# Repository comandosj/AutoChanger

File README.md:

AutoChanger - A Knitting Machine Auto Colour Changer to replace a Brother KRC-900
=============

This project was designed to provide a lower cost replacement for the commercial auto colour changer available from Brother for their 1980's electronic knitting machines.

You can read about the progress of this design at the following links:

[Building a better colour changer - Part 1 - Designing Hardware](http://heartofpluto.co/2017/04/25/building-a-better-colour-changer-part-1-designing-hardware/)

[Building a better colour changer - Part 2 - Firing the lasers](http://heartofpluto.co/2017/05/08/building-a-better-colour-changer-part-2-firing-the-lasers/)

[Building a Better Colour Changer  Part 3  Revising the design](http://heartofpluto.co/2017/10/21/building-a-better-colour-changer-part-3-revising-the-design/)

The Arduino Nano based controller.

[Schematic Design](Controller/AutoChanger.pdf?raw=true "Schematic")

FEATURES
--------

* Arduino Uno compatible.
* Automatically change between 4 different colours.
* Audio guides.
* Programable colour order.

CREDITS
------------

This project was designed in 2017 by John and Sarah Spencer
 - [John Spencer](https://github.com/mage0r)
 - [Sarah Spencer](https://github.com/chixor)

Check us out at [Heart Of Pluto](http://heartofpluto.co)

Made at hackmelbourne.org!

SPECIAL THANKS
------------

To the HackMelbourne (CCHS, http://hackmelbourne.org) community of Melbourne, Australia.

To all other open-source developers whose countless hours supported every other aspect of this design.

DISTRIBUTION
------------
The specific terms of distribution of this project are governed by the
license referenced below. Please contact the copyright owner if you wish to modify the board for distribution. Please utilize this design for personal or research projects. Please acknowledge all contributors.

LICENSE
-------
Licensed under the TAPR Open Hardware License (www.tapr.org/OHL).
The "license" sub-folder also contains a copy of this license in plain text format.

Copyright John Spencer, Sarah Spencer, 2017

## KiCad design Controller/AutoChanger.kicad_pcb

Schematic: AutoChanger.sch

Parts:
C1, C2, C10, C11, C12, C13: 1uF; C_0603_HandSoldering
C8: 100nF; C_0603_HandSoldering
P1: CONNECT; Pin_Header_Straight_2x02_Pitch2.54mm
P3: 1; Pin_Header_Straight_1x03_Pitch2.54mm
P4: 2; Pin_Header_Straight_1x03_Pitch2.54mm
P5: 3; Pin_Header_Straight_1x03_Pitch2.54mm
P6: 4; Pin_Header_Straight_1x03_Pitch2.54mm
P7: 6; Pin_Header_Straight_1x03_Pitch2.54mm
P8, P9: M3; 1pin
P10, P11: SENSOR; Pin_Header_Straight_1x03_Pitch2.54mm
P12: LOGO; logo
P13: 5; Pin_Header_Straight_1x03_Pitch2.54mm
R1, R5, R7, R8, R9, R10, R11: 10K; R_0603_HandSoldering
R4: 220R; R_0603_HandSoldering
R12: 100; R_0603_HandSoldering
SP1: SPEAKER; Buzzer_12x9.5RM7.6
SW1: RESET; SW_PUSH_SMALL
SW2: 1; SW_PUSH_SMALL
SW3: 2; SW_PUSH_SMALL
SW4: 3; SW_PUSH_SMALL
SW5: 4; SW_PUSH_SMALL
SW6: PGRM; SW_PUSH_SMALL
U1: arduino_nano; nano
U2: STATUS; LED_WS2812B-PLCC4
U3: ITR9606-F; ITR9606

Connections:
+5V: C1.2, C2.2, C8.1, C10.2, C11.2, C12.2, C13.2, P1.4, P3.2, P4.2, P5.2, P6.2, P7.2, P10.1, P11.1, P13.2, R1.1, R4.1, R7.1, R8.1, R9.1, R10.1, R11.1, U1.12, U2.1; also elsewhere on the board
/3V3: U1.2
/A0: P3.3, U1.4
/A1: P4.3, U1.5
/A2: P5.3, U1.6
/A3: P6.3, U1.7
/A4: P13.3, U1.8
/A5: P7.3, U1.9
/A6: U1.10
/A7: U1.11
/AREF: U1.3
/D2: U1.20
/D3: R12.1, U1.21
/D4: U1.22, U2.4
/D5: P1.2, U1.23
/D6: R11.2, SW6.1, U1.24
/D7: R10.2, SW5.1, U1.25
/D8: R9.2, SW4.1, U1.26
/D9: R8.2, SW3.1, U1.27
/D10: R7.2, SW2.1, U1.28
/D11: P1.3, U1.29
/D12: U1.30
/D13: P10.2, P11.2, R5.1, U1.1, U3.4
/RESET: R1.2, SW1.1, U1.13, U1.18
/RXD: U1.17
/TXD: U1.16
/VIN: U1.15
GND: C1.1, C2.1, C8.2, C10.1, C11.1, C12.1, C13.1, P1.1, P3.1, P4.1, P5.1, P6.1, P7.1, P10.3, P11.3, P13.1, R5.2, SP1.1, SW1.2, SW2.2, SW3.2, SW4.2, SW5.2, SW6.2, U1.14, U1.19, U2.3, U3.2
unnamed 30: U3.3; also elsewhere on the board
unnamed: R4.2, U3.1
unnamed: R12.2, SP1.2

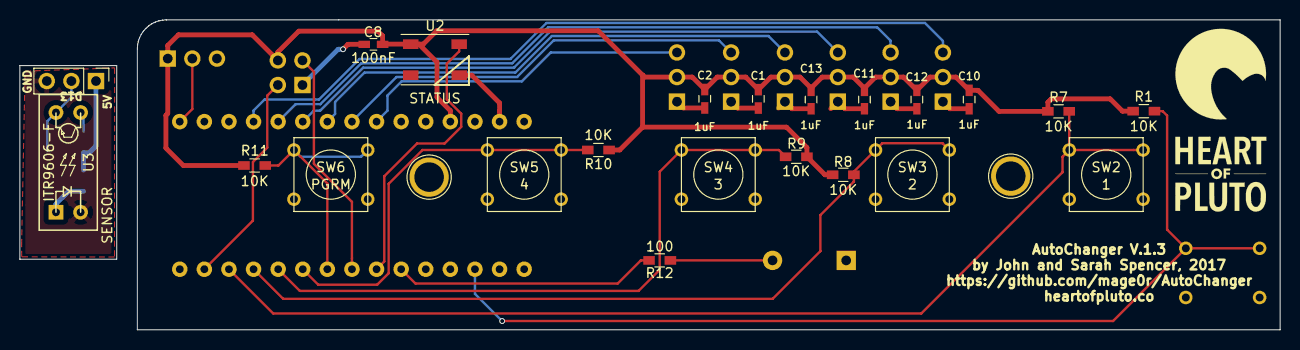
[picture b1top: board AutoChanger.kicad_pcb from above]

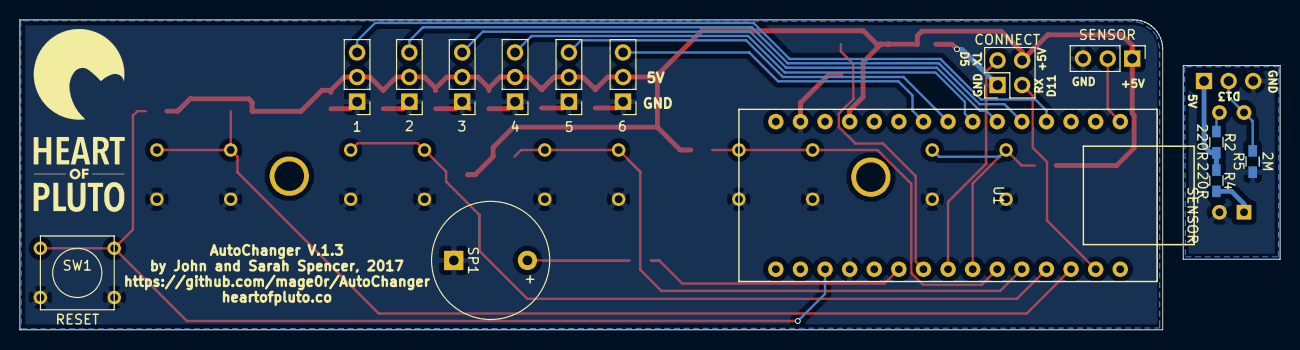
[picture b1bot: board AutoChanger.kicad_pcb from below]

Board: 2 copper layers, 130.1 x 32.0 mm, 40 parts (15 on the bottom side), 22 nets.

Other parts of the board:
P12#2: LOGO; logo
R2: 220R; R_0603_HandSoldering

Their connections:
+5V: R2.1; also elsewhere on the board
unnamed 30: R2.2; also elsewhere on the board

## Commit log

2017-05-14 :confetti_ball: Added .gitattributes & .gitignore files
2017-05-14 Initial Upload
2017-05-19 Added a buzzer and moved pins.
2017-05-27 Adding schematic pdfs and license
2017-05-27 Hardware design Sketchup files added
2017-05-27 Added Readme file.
2017-05-27 typos
2017-05-27 Updated design.
2017-05-28 Optical pickup was too small in design
2017-06-25 Updated board design.
    Heaps more caps. Thanks @projectgus
2017-06-25 Revised the size of gear shaft.
2017-08-19 Updated hardware design
    Getting closer and closer to having all the angles right.
2017-08-25 Updated design
2017-09-11 Updated circuit board
2017-10-05 Updated version
2017-10-19 New Nano version
2017-10-19 updated submodules
2017-10-19 Updated 3d settings.
2017-10-19 Adding Software
2018-09-05 Updated designs across the board
    So, lots of small changes as I've tweaked the design.
    In order to improve manufacturing, I've changed to 3d printing the main body.
2018-09-05 Lets ignore stl files
2018-10-23 Updated sub board
2018-10-23 File cleanup
2018-10-23 Cleaned up readme
2018-10-23 Updated image link.
2018-11-09 Big code update. Feature Complete maybe?
    The firmware now allows full pattern reprogramming.
    As a special bonus, in manual mode arms can be toggled.
    As a special, special bonus, you can reset the program to the default by
    holding the number buttons while starting the unit!
2018-11-09 Debounce delay way to high
    So, playing with deboucing and did a test to set it to stupid large
    number.
    Forgot to reset that....
